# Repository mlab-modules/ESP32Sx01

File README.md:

# ESP32Sx01 - ESP32-S3 MLAB module

## Description

ESP32Sx01 is a compact MLAB development module based on the ESP32-S3-MINI-1 microcontroller module from Espressif. The module provides a complete development platform for IoT applications with WiFi and Bluetooth connectivity.

## Key Features

* **Microcontroller**: ESP32-S3-MINI-1
  * Dual-core Xtensa® 32-bit LX7 microprocessor
  * WiFi 802.11 b/g/n (2.4 GHz)
  * Bluetooth® 5 (LE)
  * Up to 8 MB Flash
  * Optional 2 MB PSRAM
* **USB Connectivity**: 2x USB Type-C connectors
  * USB programming and debugging
  * ESD protection (USBLC6-2SC6)
* **Power Supply**:
  * Onboard 3.3V regulator (NCP1117-3.3)
  * Input voltage: +5V via USB or external connector
  * Output: +3.3V for ESP32-S3 and peripherals
* **User Interface**:
  * Reset button
  * Power LED (Green)
  * User LED (Red)
* **Expansion**: 
  * MLAB standard connectors
  * Multiple pin headers for GPIO access
  * Crystal oscillator for precise timing
* **Protection**:
  * USB ESD protection

## Applications

* IoT sensor nodes
* WiFi/Bluetooth gateways
* Home automation controllers
* Wireless data logging
* Educational projects
* Rapid prototyping

## Pinout
The module provides access to ESP32-S3 GPIO pins through standard MLAB connectors and pin headers. Refer to the schematic for detailed pinout information.

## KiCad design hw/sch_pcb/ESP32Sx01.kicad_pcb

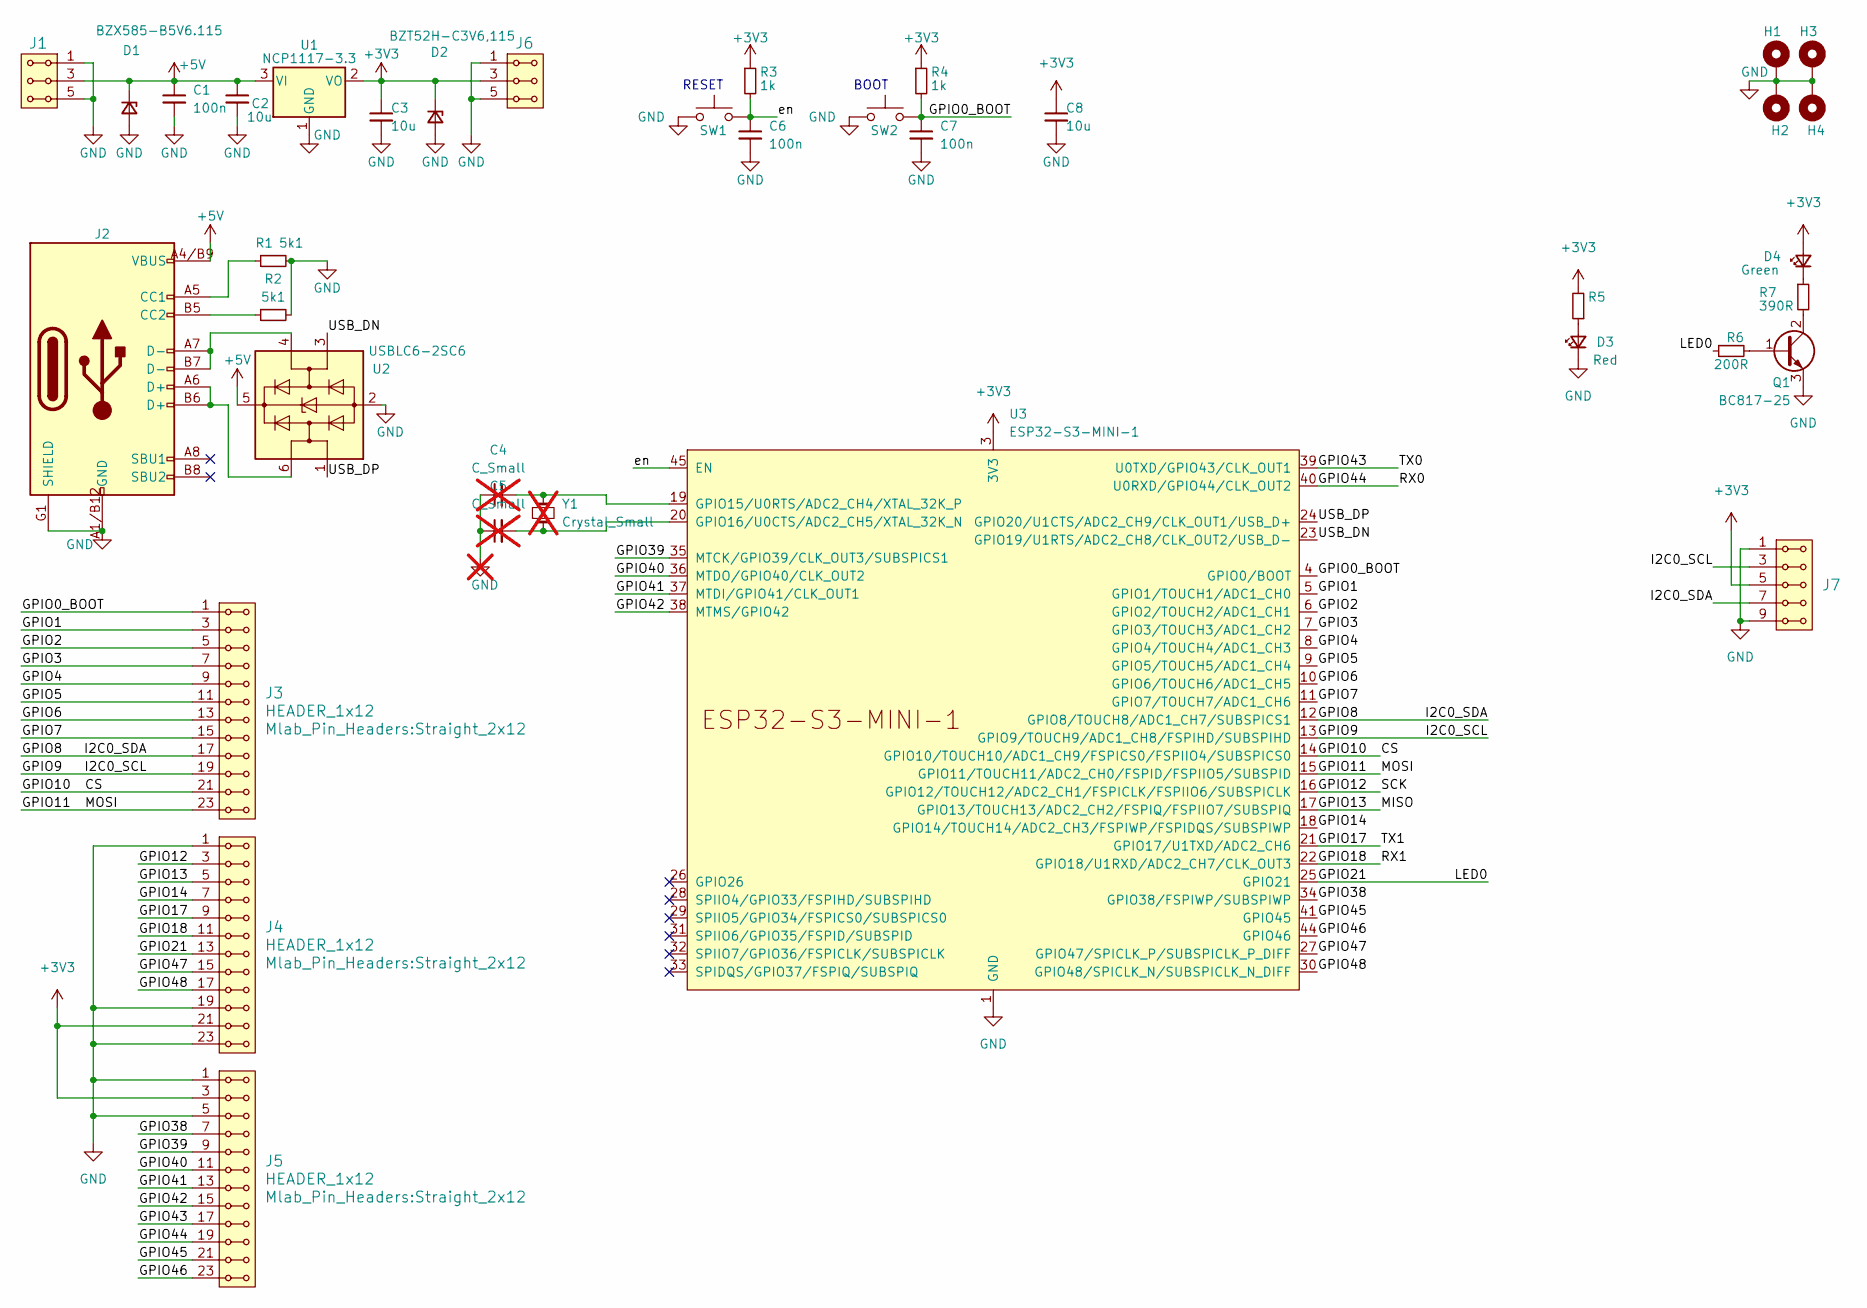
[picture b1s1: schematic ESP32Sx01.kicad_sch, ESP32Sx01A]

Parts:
C1, C6, C7: 100n; C_0805_2012Metric
C2, C3, C8: 10u; C_0805_2012Metric
C4, C5: C_Small; C_0805_2012Metric; not fitted
D1: BZX585-B5V6.115; D_SOD-523
D2: BZT52H-C3V6,115; Nexperia_CFP3_SOD-123W
D3: Red; LED_1206_KPTR
D4: Green; LED_1206_KPTR
H1, H2, H3, H4: MountingHole_Pad; MountingHole_3.2mm_M3_Pad_Via
J1, J6: HEADER_1x03; Straight_2x03
J2: USBC_USB4105-GF-A; USBC GCT_USB4105-GF-A
J3, J4, J5: HEADER_1x12; Straight_2x12
J7: HEADER_2x05; Straight_2x05
Q1: BC817-25; SOT-23
R1, R2: 5k1; R_0805_2012Metric
R3, R4: 1k; R_0805_2012Metric
R5, R6: 200R; R_0805_2012Metric
R7: 390R; R_0805_2012Metric
SW1, SW2: 434133025816; SW_Push_1P1T_NO_Vertical_Wuerth_434133025816
U1: NCP1117-3.3; SOT-223-3_TabPin2
U2: USBLC6-2SC6; SOT-23-6
U3: ESP32-S3-MINI-1
Y1: Crystal_Small; ABS07; not fitted

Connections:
+3V3: C3.1, C8.1, D2.1 (K), D4.2 (A), J4.21, J4.22, J5.3, J5.4, J6.3, J6.4, J7.5, J7.6, R3.1, R4.1, R5.2, U1.2 (VO), U3.3 (3V3)
+5V: C1.1, C2.1, D1.1 (K), J1.3, J1.4, J2.A4/B9 (VBUS), J2.B4/A9 (VBUS), U1.3 (VI), U2.5 (VBUS)
/CS: J3.21, J3.22, U3.14 (GPIO10/TOUCH10/ADC1_CH9/FSPICS0/FSPIIO4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)
/GPIO0_BOOT: C7.1, J3.1, J3.2, R4.2, SW2.2, U3.4 (GPIO0/BOOT)
/GPIO1: J3.3, J3.4, U3.5 (GPIO1/TOUCH1/ADC1_CH0)
/GPIO2: J3.5, J3.6, U3.6 (GPIO2/TOUCH2/ADC1_CH1)
/GPIO3: J3.7, J3.8, U3.7 (GPIO3/TOUCH3/ADC1_CH2)
/GPIO4: J3.9, J3.10, U3.8 (GPIO4/TOUCH4/ADC1_CH3)
/GPIO5: J3.11, J3.12, U3.9 (GPIO5/TOUCH5/ADC1_CH4)
/GPIO6: J3.13, J3.14, U3.10 (GPIO6/TOUCH6/ADC1_CH5)
/GPIO7: J3.15, J3.16, U3.11 (GPIO7/TOUCH7/ADC1_CH6)
/GPIO8: J3.17, J3.18, J7.7, J7.8, U3.12 (GPIO8/TOUCH8/ADC1_CH7/SUBSPICS1)
/GPIO9: J3.19, J3.20, J7.3, J7.4, U3.13 (GPIO9/TOUCH9/ADC1_CH8/FSPIHD/SUBSPIHD)
/GPIO11: J3.23, J3.24, U3.15 (GPIO11/TOUCH11/ADC2_CH0/FSPID/FSPIIO5/S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)
/GPIO12: J4.3, J4.4, U3.16 (GPIO12/TOUCH12/ADC2_CH1/FSPICLK/FSPIIO6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)
/GPIO13: J4.5, J4.6, U3.17 (GPIO13/TOUCH13/ADC2_CH2/FSPIQ/FSPIIO7/S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)
/GPIO14: J4.7, J4.8, U3.18 (GPIO14/TOUCH14/ADC2_CH3/FSPIWP/FSPIDQS/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)
/GPIO17: J4.9, J4.10, U3.21 (GPIO17/U1TXD/ADC2_CH6)
/GPIO18: J4.11, J4.12, U3.22 (GPIO18/U1RXD/ADC2_CH7/CLK_OUT3)
/GPIO21: J4.13, J4.14, R6.1, U3.25 (GPIO21)
/GPIO38: J5.7, J5.8, U3.34 (GPIO38/FSPIWP/SUBSPIWP)
/GPIO39: J5.9, J5.10, U3.35 (MTCK/GPIO39/CLK_OUT3/SUBSPICS1)
/GPIO40: J5.11, J5.12, U3.36 (MTDO/GPIO40/CLK_OUT2)
/GPIO41: J5.13, J5.14, U3.37 (MTDI/GPIO41/CLK_OUT1)
/GPIO42: J5.15, J5.16, U3.38 (MTMS/GPIO42)
/GPIO43: J5.17, J5.18, U3.39 (U0TXD/GPIO43/CLK_OUT1)
/GPIO44: J5.19, J5.20, U3.40 (U0RXD/GPIO44/CLK_OUT2)
/GPIO45: J5.21, J5.22, U3.41 (GPIO45)
/GPIO46: J5.23, J5.24, U3.44 (GPIO46)
/GPIO47: J4.15, J4.16, U3.27 (GPIO47/SPICLK_P/SUBSPICLK_P_DIFF)
/GPIO48: J4.17, J4.18, U3.30 (GPIO48/SPICLK_N/SUBSPICLK_N_DIFF)
/USB_DN: U2.3 (I/O2), U3.23 (GPIO19/U1RTS/ADC2_CH8/CLK_OUT2/USB_D-)
/USB_DP: U2.1 (I/O1), U3.24 (GPIO20/U1CTS/ADC2_CH9/CLK_OUT1/USB_D+)
/en: C6.1, R3.2, SW1.2, U3.45 (EN)
GND: C1.2, C2.2, C3.2, C4.1, C5.1, C6.2, C7.2, C8.2, D1.2 (A), D2.2 (A), D3.1 (K), H1.1, H2.1, H3.1, H4.1, J1.1, J1.2, J1.5, J1.6, J2.A1/B12 (GND), J2.B1/A12 (GND), J2.G1 (SHIELD), J2.G2 (SHIELD), J2.G3 (SHIELD), J2.G4 (SHIELD), J4.1, J4.2, J4.19, J4.20, J4.23, J4.24, J5.1, J5.2, J5.5, J5.6, J6.1, J6.2, J6.5, J6.6, J7.1, J7.2, J7.9, J7.10, Q1.3 (E), R1.2, R2.2, SW1.1, SW2.1, U1.1 (GND), U2.2 (GND), U3.1 (GND), U3.2 (GND), U3.42 (GND), U3.43 (GND), U3.46 (GND), U3.47 (GND), U3.48 (GND), U3.49 (GND), U3.50 (GND), U3.51 (GND), U3.52 (GND), U3.53 (GND), U3.54 (GND), U3.55 (GND), U3.56 (GND), U3.57 (GND), U3.58 (GND), U3.59 (GND), U3.60 (GND), U3.61 (GND), U3.62 (GND), U3.63 (GND), U3.64 (GND), U3.65 (GND)
unnamed: D3.2 (A), R5.1
unnamed: D4.1 (K), R7.1
unnamed: J2.A5 (CC1), R1.1
unnamed: J2.B5 (CC2), R2.1
unnamed: J2.A6 (D+), J2.B6 (D+), U2.6 (I/O1)
unnamed: J2.A7 (D-), J2.B7 (D-), U2.4 (I/O2)
unnamed: Q1.1 (B), R6.2
unnamed: Q1.2 (C), R7.2
unnamed: C4.2, U3.19 (GPIO15/U0RTS/ADC2_CH4/XTAL_32K_P), Y1.1
unnamed: C5.2, U3.20 (GPIO16/U0CTS/ADC2_CH5/XTAL_32K_N), Y1.2

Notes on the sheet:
RESET
BOOT

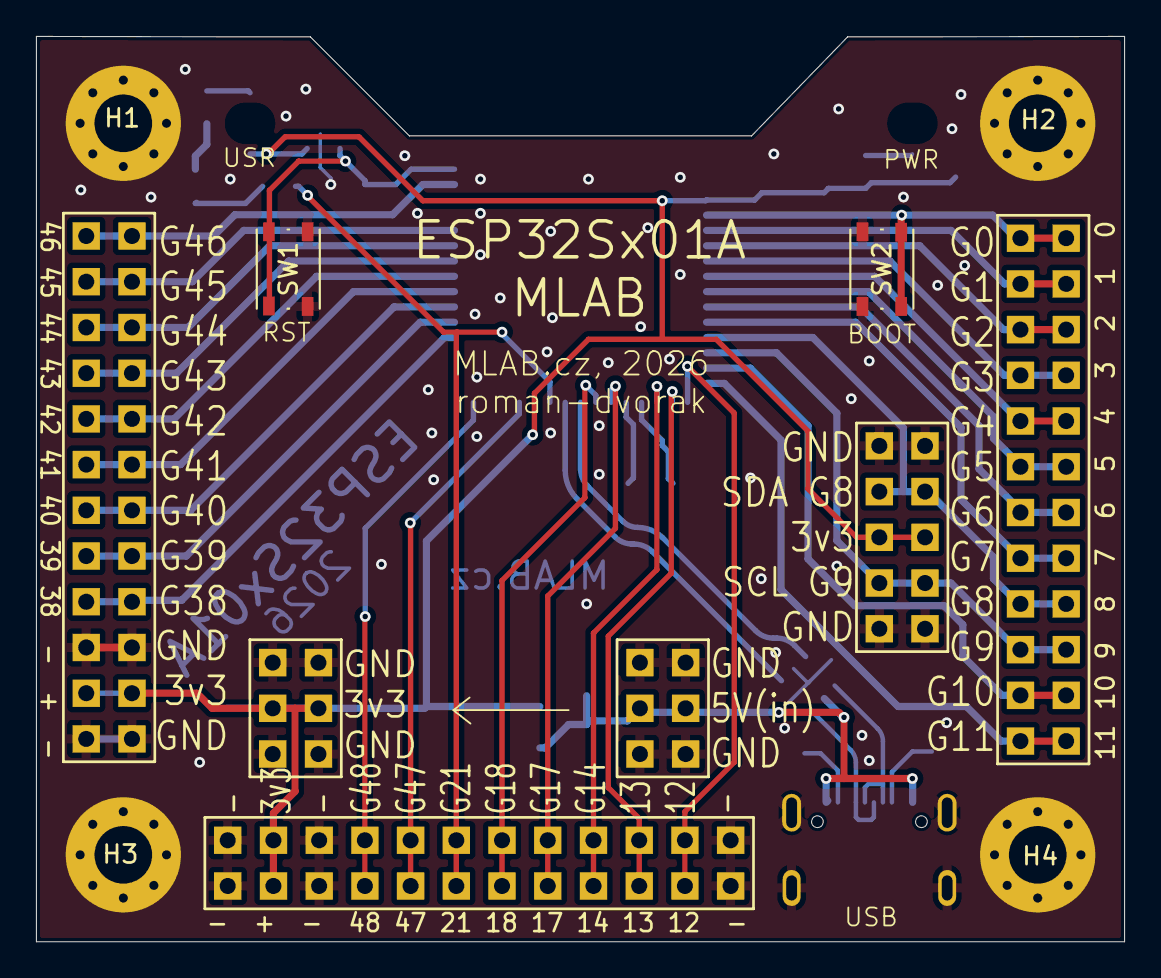
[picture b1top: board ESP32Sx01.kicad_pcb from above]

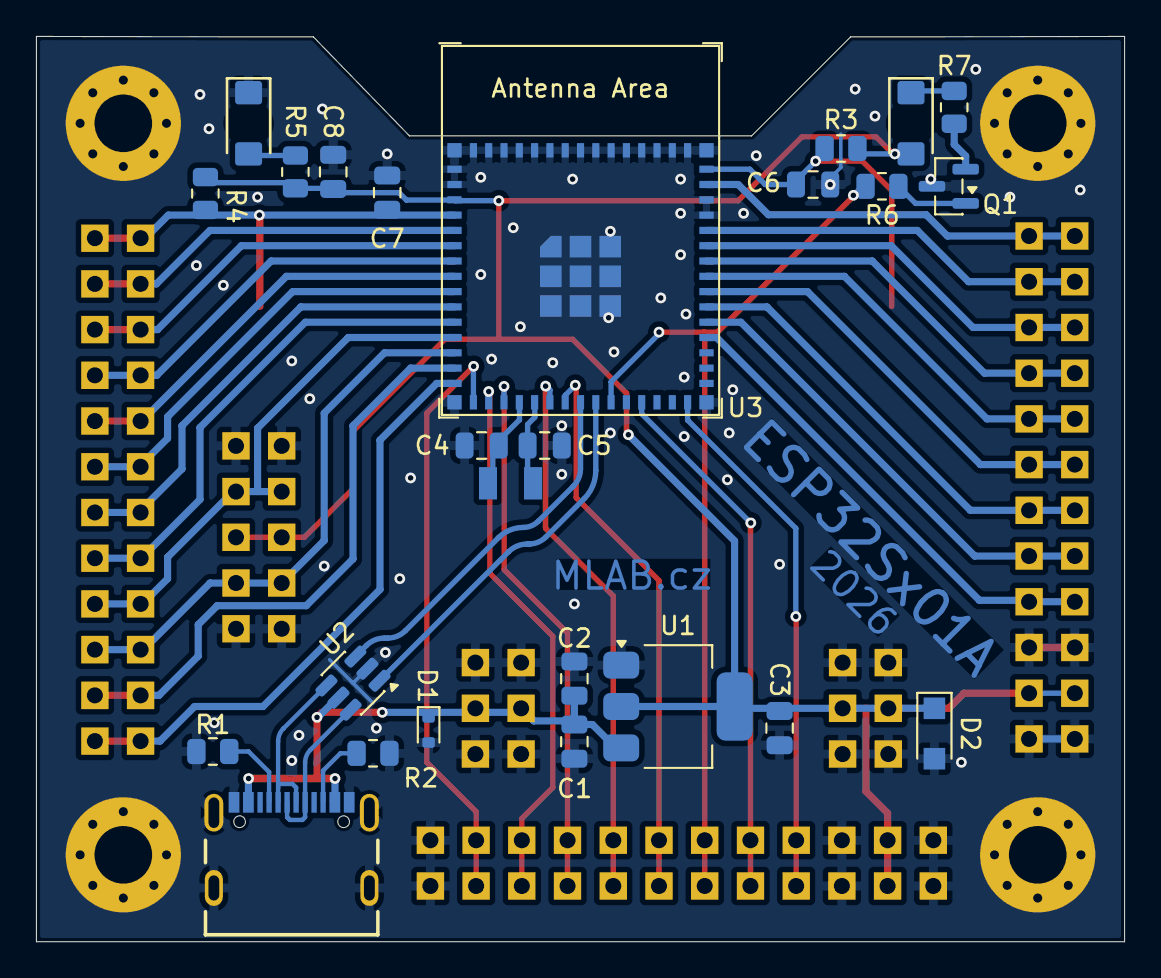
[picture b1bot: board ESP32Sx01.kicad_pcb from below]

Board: 2 copper layers, 60.5 x 50.3 mm, 37 parts (25 on the bottom side), 45 nets.

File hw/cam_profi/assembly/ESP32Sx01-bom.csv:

Component,Description,Part,References,Value,Footprint,Quantity Per PCB,Datasheet,obchod
1,"Unpolarized capacitor, small symbol",C_Small,C1C6C7,100n,C_0805_2012Metric,3,~,TME
2,"Unpolarized capacitor, small symbol",C_Small,C2C3C8,10u,C_0805_2012Metric,3,~,TME
3,"Light emitting diode, small symbol",LED_Small,D2,Green,LED_1206_KPTR,1,~,OK
4,"Light emitting diode, small symbol",LED_Small,D1,Red,LED_1206_KPTR,1,~,OK
5,"2x03 2.54 mm pitch header, 2 pins next to each other are connected",HEADER_2x03_PARALLEL,J1J6,HEADER_1x03,Straight_2x03,2,,
6,"2x12 2.54 mm pitch header, 2 pins next to each other are connected",HEADER_2x12_PARALLEL,J3J4J5,HEADER_1x12,Straight_2x12,3,,
7,"2x05 2.54 mm pitch header, 2 pins next to each other are connected",HEADER_2x05_PARALLEL,J7,HEADER_2x05,Straight_2x05,1,,
8,USB 2.0-only Type-C Receptacle connector,USBC_USB4105-GF-A,J2,USBC_USB4105-GF-A,USBC GCT_USB4105-GF-A,1,https://www.usb.org/sites/default/files/documents/usb_type-c.zip,OK
9,"NPN transistor, base/collector/emitter",Q_NPN_BCE,Q1,BC817-25,SOT-23,1,~,TME
10,"Resistor, small symbol",R_Small,R5R6,200R,R_0805_2012Metric,2,~,TME
11,"Resistor, small symbol",R_Small,R7,390R,R_0805_2012Metric,1,~,
12,"Resistor, small symbol",R_Small,R3R4,1k,R_0805_2012Metric,2,~,TME
13,"Resistor, small symbol",R_Small,R1R2,5k1,R_0805_2012Metric,2,~,TME
14,"Push button switch, generic, two pins",SW_Push,SW1SW2,434133025816,SW_Push_1P1T_NO_Vertical_Wuerth_434133025816,2,~,TME
15,"Smallsized module supporting 2.4 GHz WiFi (802.11 b/g/n) and Bluetooth ® 5 (LE) Built around ESP32S3 series of SoCs, Xtensa ® dualcore 32bit LX7 microprocessor Flash up to 8 MB, optional 2 MB PSRAM in chip package 39 GPIOs, rich set of peripherals Onboard PCB antenna or external antenna connector",ESP32-S3-MINI-1,U3,ESP32-S3-MINI-1,ESP32-S3-MINI-1,1,https://www.espressif.com/sites/default/files/documentation/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,
16,"1A Low drop-out regulator, Fixed Output 3.3V, SOT-223",NCP1117-3.3_SOT223,U1,NCP1117-3.3,SOT-223-3_TabPin2,1,http://www.onsemi.com/pub_link/Collateral/NCP1117-D.PDF,TME
17,"Very low capacitance ESD protection diode, 2 data-line, SOT-23-6",USBLC6-2SC6,U2,USBLC6-2SC6,SOT-23-6,1,https://www.st.com/resource/en/datasheet/usblc6-2.pdf,TME

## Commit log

2026-01-26 Update metadata files
2026-01-27 Update title blocks.
2026-01-27 Update actions products
2026-01-28 Update workflow files
2026-02-13 Update of PCB design
2026-02-13 finishing PCB design
2026-02-13 add simple README
2026-02-13 move boot button
2026-02-13 Update image path for module photo in README
2026-02-13 rotate LED to maintain same orientation
2026-02-13 minor layout modifications
2026-02-14 solve missing anotation in schematics
2026-02-15 add polarity-swap protection
2026-02-15 Automatic update of KiCAD outputs
2026-02-15 Cleanup fab layer. Resolve DRC errors.
2026-02-15 Update metadata.yaml
    Change status to active.
2026-02-20 Update UST_IDs.
2026-02-21 Add UST_ID for Y1.
